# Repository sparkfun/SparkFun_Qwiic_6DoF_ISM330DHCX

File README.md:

SparkFun Qwiic 6DoF ISM330DHCX
========================================

<table class="table table-hover table-striped table-bordered">
  <tr align="center">
   <td></td>
   <td></td>
  </tr>
  <tr align="center">
   <td><i>SparkFun Qwiic 6DoF - ISM330DHCX [<a href="https://www.sparkfun.com/products/19764">SEN-19764</a>]</i></td>
   <td><i>SparkFun Micro 6DoF IMU - ISM330DHCX (Qwiic) [<a href="https://www.sparkfun.com/products/20176">SEN-20176</a>]</i></td>
  </tr>
</table>

Do you need 6 degrees of freedom? We do! Behold the SparkFun Qwiic 6DoF - ISM330DHCX - a Qwiic enabled 1x1" breakout featuring STMicroelectronics' ISM330DHCX; a high-performance 3D digital accelerometer and 3D digital gyroscope tailored for Industry 4.0 applications such as platform, optical image, and lens stabilization, robotics and industrial automation, navigations systems, and vibration monitoring and compensation. 

This bad boy has a full-scale acceleration range of ±2/±4/±8/±16 g and a wide angular rate range of ±125/±250/±500/±1000/±2000/±4000 dps that enable its usage in a broad range of applications. Multiple modes allow for peripheral only, secondary I<sup>2</sup>C, and and auxiliary 3 or 4 wire serial interface. An unmatched set of embedded features (Machine Learning Core, programmable FSM, FIFO, sensor hub, event decoding and interrupts) are enablers for implementing smart and complex sensor nodes which deliver high performance at very low power.  

The dual Qwiic connectors on this little breakout make setting it up a breeze. Simply supply the accelerometer with power and communication via the Qwiic connector to your chosen Qwiic development board and you will be good to go. Should you prefer to use them, we've also broken out all the ISM330DHCX pin functionality to GPIO along either side of the board. 

Repository Contents
-------------------

* **/Documentation** - Data sheets, additional product information
* **/Hardware** - Eagle design files (.brd, .sch)
* **/Production** - Production panel files (.brd)

Documentation
--------------

* **[Library](https://github.com/sparkfun/SparkFun_6DoF_ISM330DHCX_Arduino_Library)** - Arduino library for the SparkFun Qwiic 6DoF - ISM330DHCX.
* **[Hookup Guide](https://sparkle.sparkfun.com/sparkle/learn_tutorials/2484)** - Basic hookup guide for the SparkFun Qwiic 6DoF - ISM330DHCX.

Product Versions
--------------

* [SEN-20176](https://www.sparkfun.com/products/20176) - SparkFun red version, micro size
* [SEN-19764](https://www.sparkfun.com/products/19764) - SparkFun red version

License Information
-------------------

This product is _**open source**_! 

Please review the LICENSE.md file for license information. 

If you have any questions or concerns on licensing, please contact technical support on our [SparkFun forums](https://forum.sparkfun.com/viewforum.php?f=152).

Distributed as-is; no warranty is given.

- Your friends at SparkFun.

_<COLLABORATION CREDIT>_

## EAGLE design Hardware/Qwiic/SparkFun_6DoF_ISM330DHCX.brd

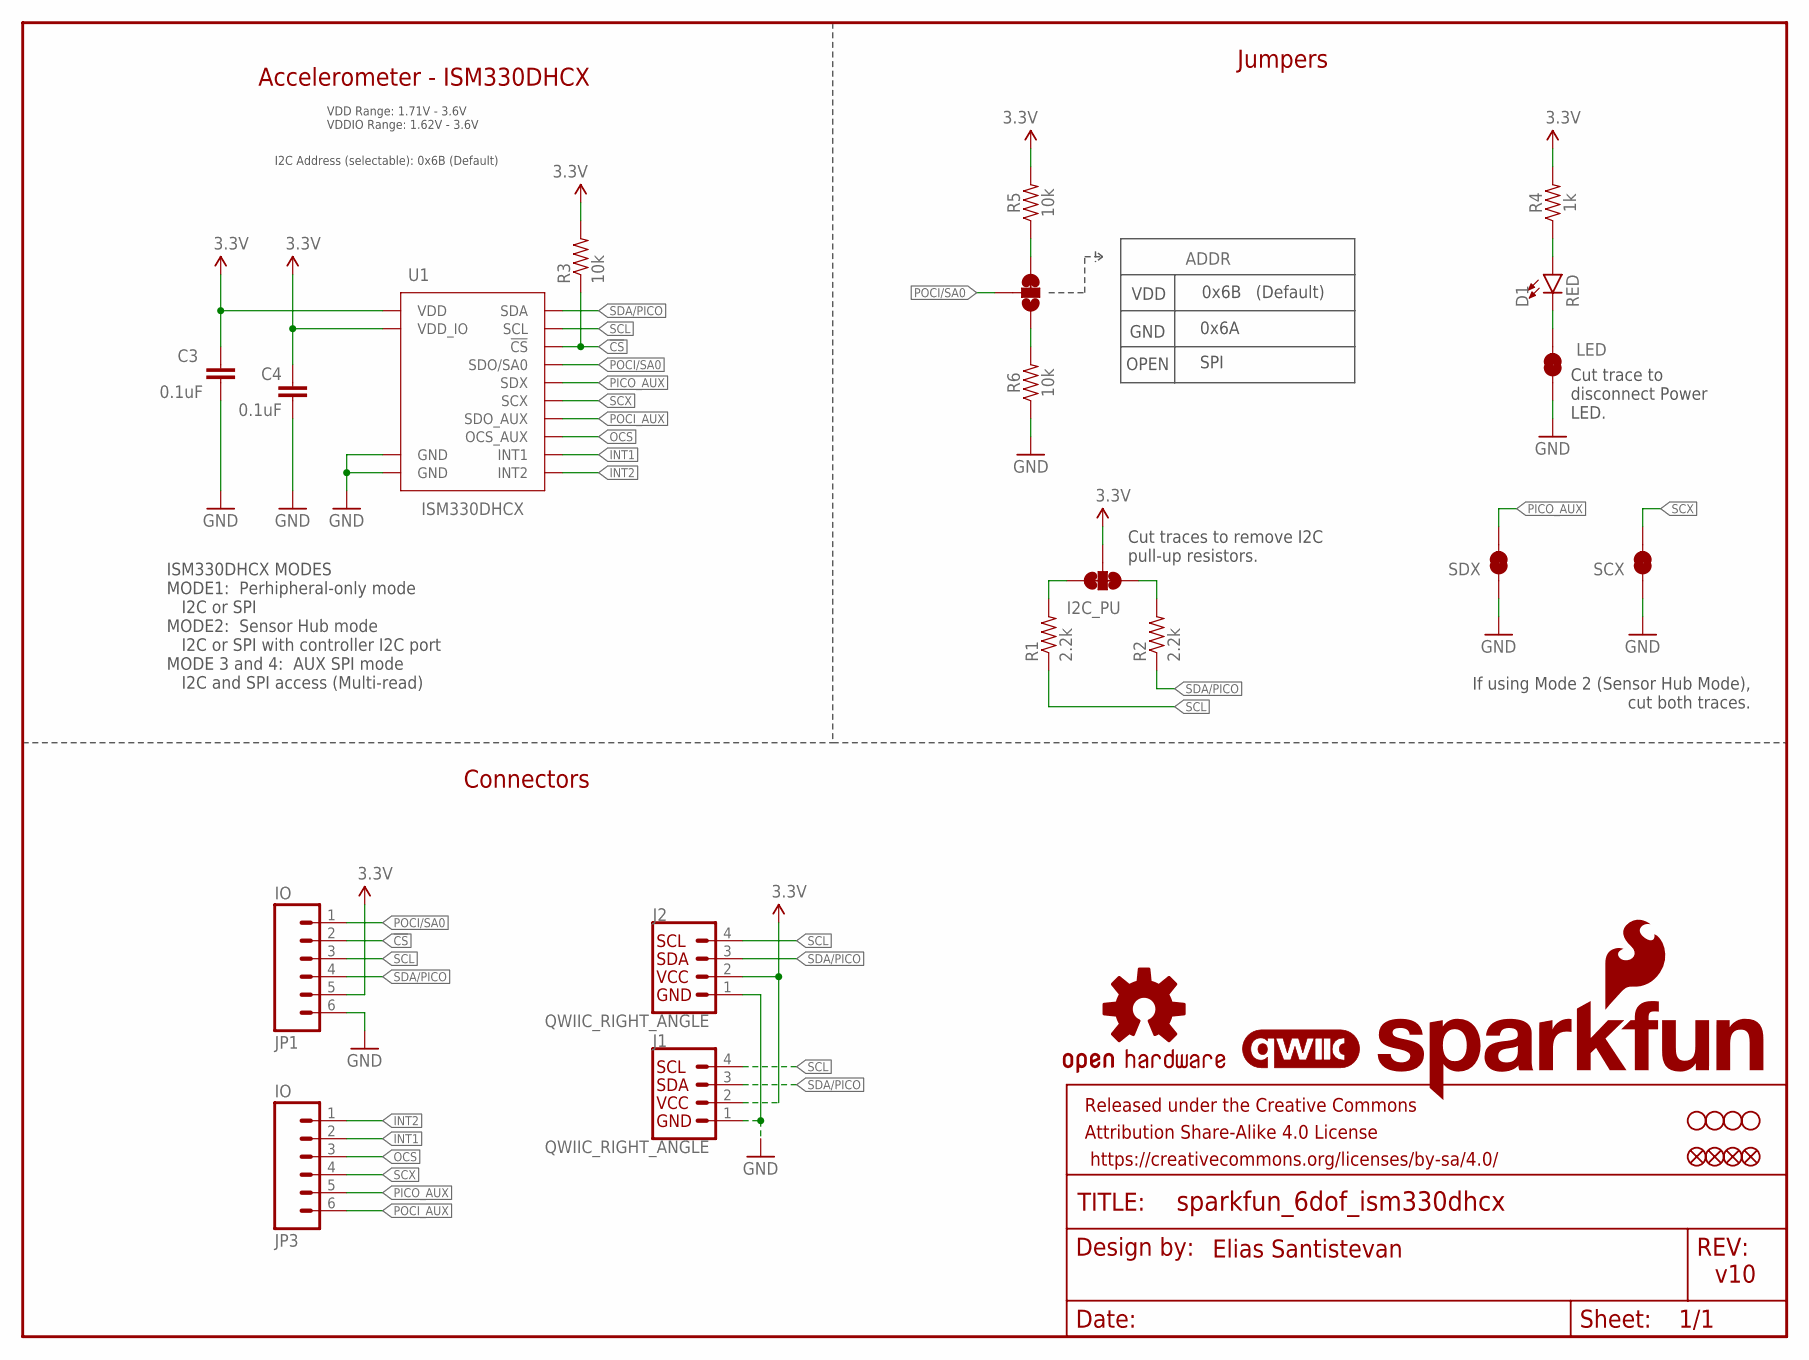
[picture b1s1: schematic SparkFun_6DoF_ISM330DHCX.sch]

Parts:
ADDR: JUMPER-SMT_3_1-NC_TRACE_SILK; SMT-JUMPER_3_1-NC_TRACE_SILK
C3, C4: 0.1uF; 0603
D1: RED; LED-0603
FD1, FD2: FIDUCIALUFIDUCIAL; FIDUCIAL-MICRO
FID1, FID2: FIDUCIALUFIDUCIAL; FIDUCIAL-MICRO
FRAME1: FRAME-LETTER; CREATIVE_COMMONS
I2C_PU: S_MODE; SMT-JUMPER_3_2-NC_TRACE_SILK
J1, J2: QWIIC_RIGHT_ANGLE; JST04_1MM_RA
JP1, JP3: IO; 1X06_NO_SILK
LED: JUMPER-SMT_2_NC_TRACE_SILK; SMT-JUMPER_2_NC_TRACE_SILK
LOGO1: QWIIC_LOGO_4MM; QWIIC_4MM
LOGO2: OSHW-LOGOMINI; OSHW-LOGO-MINI
LOGO3: SFE_LOGO_NAME_FLAME.1_INCH; SFE_LOGO_NAME_FLAME_.1
R1, R2: 2.2k; 0603
R3, R5, R6: 10k; 0603
R4: 1k; 0603
SCX: JUMPER-SMT_2_NC_TRACE_SILK; SMT-JUMPER_2_NC_TRACE_SILK
SDX: JUMPER-SMT_2_NC_TRACE_SILK; SMT-JUMPER_2_NC_TRACE_SILK
STANDOFF1, STANDOFF2, STANDOFF3, STANDOFF4: STAND-OFFTIGHT; STAND-OFF-TIGHT
U1: ISM330DHCX; LGA-14L

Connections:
3.3V: C3.1, C4.1, I2C_PU.2, J1.2, J2.2, JP1.5, R3.2, R4.2, R5.2, U1.P5 (VDD_IO), U1.P8 (VDD)
!CS!: JP1.2, R3.1, U1.P12 (!CS!)
GND: C3.2, C4.2, J1.1, J2.1, JP1.6, LED.1, R6.1, SCX.1, SDX.1, U1.P6 (GND), U1.P7 (GND)
INT1: JP3.2, U1.P4 (INT1)
INT2: JP3.1, U1.P9 (INT2)
unnamed: ADDR.3, R5.1
unnamed: D1.A, R4.1
unnamed: D1.C, LED.2
unnamed: I2C_PU.1, R1.2
unnamed: I2C_PU.3, R2.2
unnamed: ADDR.1, R6.2
OCS: JP3.3, U1.P10 (OCS_AUX)
PICO_AUX: JP3.5, SDX.2, U1.P2 (SDX)
POCI/SA0: ADDR.2, JP1.1, U1.P1 (SDO/SA0)
POCI_AUX: JP3.6, U1.P11 (SDO_AUX)
SCL: J1.4, J2.4, JP1.3, R1.1, U1.P13 (SCL)
SCX: JP3.4, SCX.2, U1.P3 (SCX)
SDA/PICO: J1.3, J2.3, JP1.4, R2.1, U1.P14 (SDA)

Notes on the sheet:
Accelerometer - ISM330DHCX
If using Mode 2 (Sensor Hub Mode), cut both traces.
Cut traces to remove I2C pull-up resistors.
ISM330DHCX MODES MODE1: Perhipheral-only mode I2C or SPI MODE2: Sensor Hub mode I2C or SPI with controller I2C port MODE 3 and 4: AUX SPI mode I2C and SPI access (Multi-read)
VDD Range: 1.71V - 3.6V VDDIO Range: 1.62V - 3.6V
v10
Jumpers
Cut trace to disconnect Power LED.
Connectors
VDD
GND
OPEN
0x6B
0x6A
SPI
Elias Santistevan
(Default)
I2C Address (selectable): 0x6B (Default)

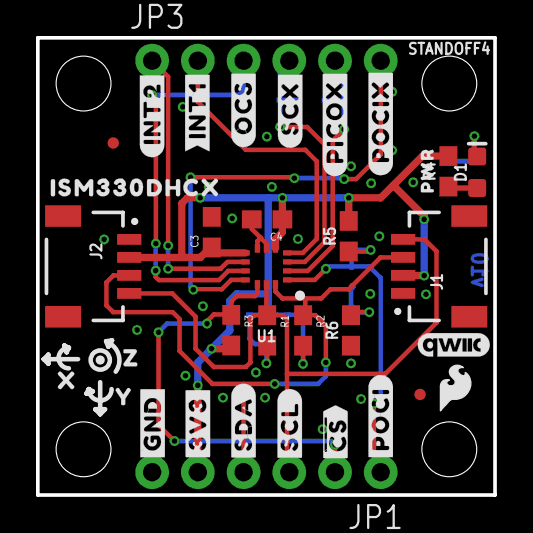
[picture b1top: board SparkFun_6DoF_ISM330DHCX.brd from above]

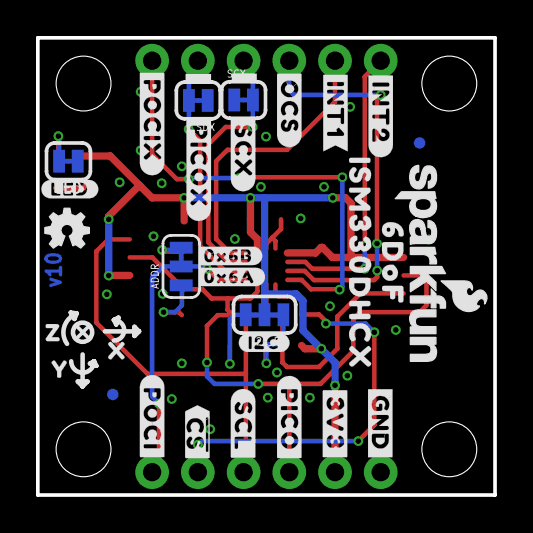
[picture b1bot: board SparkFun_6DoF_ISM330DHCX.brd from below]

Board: 2 copper layers, 25.4 x 25.4 mm, 70 parts (30 on the bottom side), 18 nets.

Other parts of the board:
U$1, U$15: #3V3#1
U$2, U$17: #GND#0
U$3: ##CS##7
U$4: #SDA#4
U$5, U$22: #SCL#5
U$6: #POCI#11
U$7, U$19: #INT1#9
U$8: #INT2#2
U$9: #OCS#8
U$10: #SCX#9
U$11: #PICOX#10
U$12: ISM330DHCX331
U$13: #0X6A#11
U$14: #0X6B#11
U$16: #LED#11
U$18: #POCI#12
U$20: #OCS#7
U$23: #SCX#8
U$24: #POCIX#8
U$25: #I2C#11
U$26: #PICO#13
U$27: ##CS##8
U$28: PWR8
U$29: SFE_LOGO_FLAME_.1
U$30: ISM330DHCX20
U$31: 6DOF12
U$32: #PICOX#9
U$33: #POCIX#7
U$34, U$37: X2114
U$35, U$38: Y2115
U$36, U$39: Z2116
U$40: #INT2#3

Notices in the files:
parts and their libraries:
SparkFun-Aesthetics: Licensing: Creative Commons ShareAlike 4.0 International - https://creativecommons.org/licenses/by-sa/4.0
SparkFun-Aesthetics: Released under the Creative Commons Attribution Share-Alike 4.0 License
SparkFun-Aesthetics: https://creativecommons.org/licenses/by-sa/4.0
